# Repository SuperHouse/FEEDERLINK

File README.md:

MGRL0816 Feeder Link
====================
Copyright 2020 SuperHouse Pty Ltd  
SuperHouse site:  www.superhouse.tv  

Connects to the bottom of 4 x MGRL0816 pick and place feeders to provide
a single connection for a 10-way IDC cable. Reduces the overall cabling
to make the machine neater.

Included are versions with different spacings to suit feeders for:

 * 8mm tape
 * 12mm tape

More information is available at:

  http://www.superhouse.tv/fl

INSTALLATION
------------
The design is saved as an EAGLE project. EAGLE PCB design software is
available from www.cadsoftusa.com free for non-commercial use. To use
this project download it and place the directory containing these files
into the "eagle" directory on your computer. Then open EAGLE and
navigate to the project.

DISTRIBUTION
------------
The specific terms of distribution of this project are governed by the
license referenced below.

LICENSE
-------
Licensed under the TAPR Open Hardware License (www.tapr.org/OHL).
The "license" folder within this repository also contains a copy of
this license in plain text format.

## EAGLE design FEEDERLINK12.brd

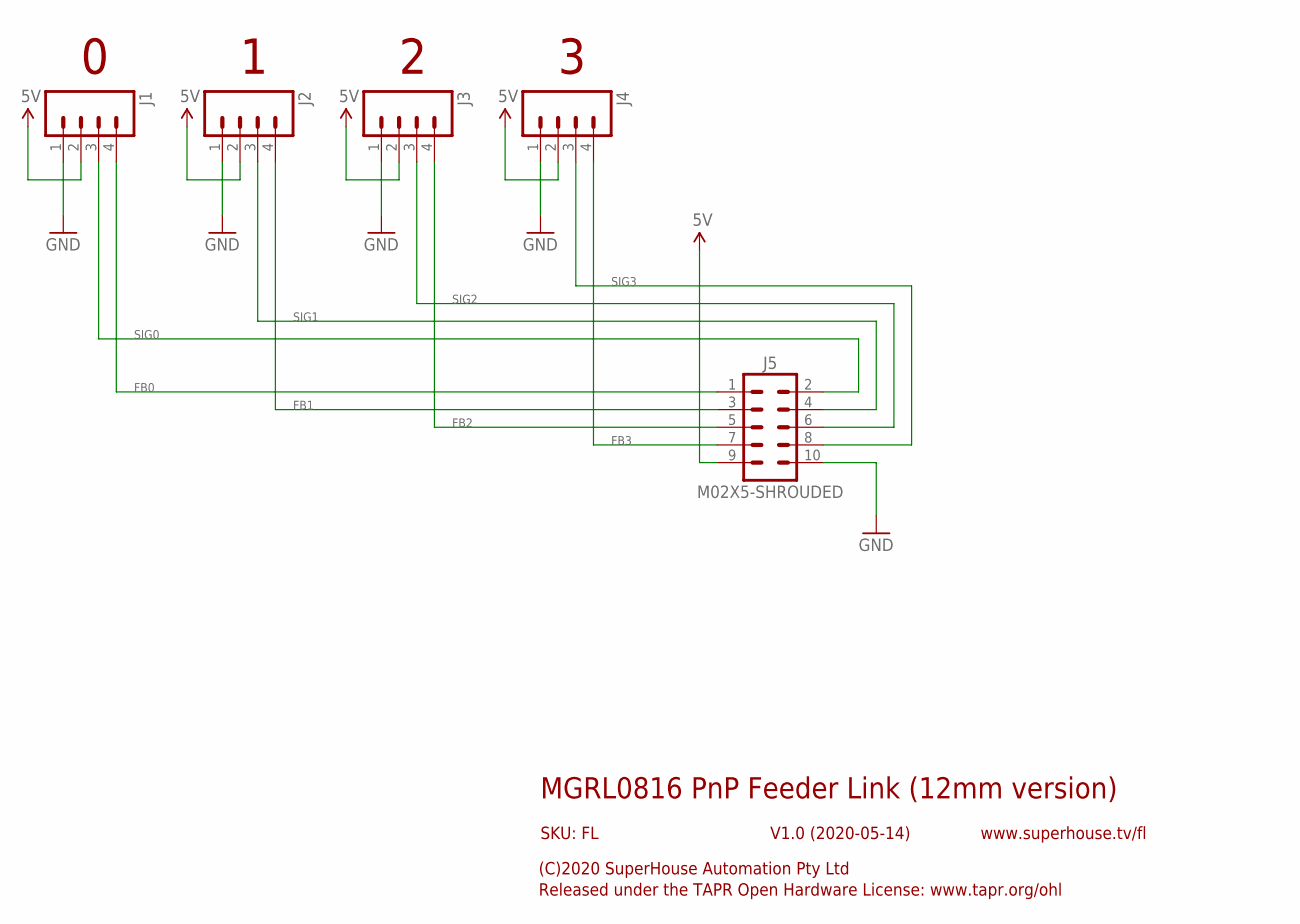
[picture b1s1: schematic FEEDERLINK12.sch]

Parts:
J1, J2, J3, J4: M04-SOCKET; 1X04-S
J5: M02X5-SHROUDED; 2X05-2.54-SHROUDED

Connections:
5V: J1.2, J2.2, J3.2, J4.2, J5.9
FB0: J1.4, J5.1
FB1: J2.4, J5.3
FB2: J3.4, J5.5
FB3: J4.4, J5.7
GND: J1.1, J2.1, J3.1, J4.1, J5.10
SIG0: J1.3, J5.2
SIG1: J2.3, J5.4
SIG2: J3.3, J5.6
SIG3: J4.3, J5.8

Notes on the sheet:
MGRL0816 PnP Feeder Link (12mm version)
V1.0 (2020-05-14)
SKU: FL
(C)2020 SuperHouse Automation Pty Ltd
Released under the TAPR Open Hardware License: www.tapr.org/ohl
www.superhouse.tv/fl

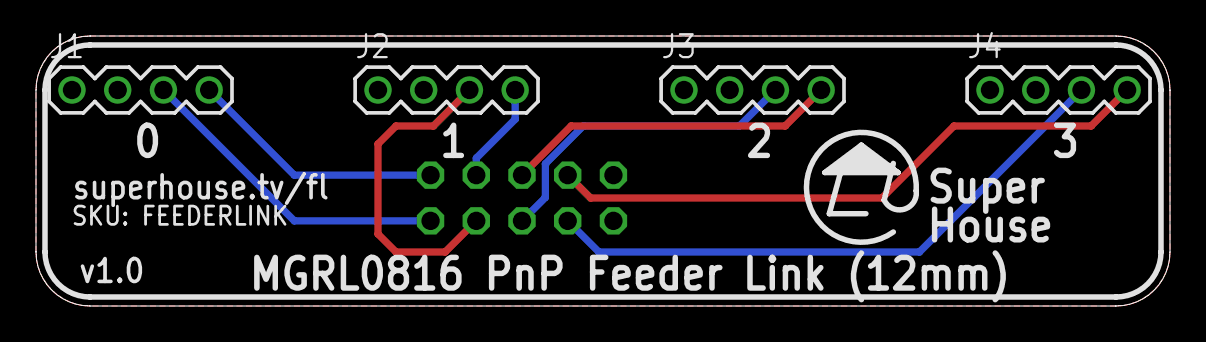
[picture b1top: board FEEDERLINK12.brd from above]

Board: 2 copper layers, 63.0 x 15.0 mm, 5 parts (1 on the bottom side), 10 nets.

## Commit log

2020-01-27 Import project for v1.0 release
2020-03-17 Changed net names to match functions
2020-05-27 Added version for 12mm feeders
2020-05-27 Renamed original project files to make it clear the are for 8mm feeders
2020-05-27 Added info about different sizes
2020-05-27 Added render
